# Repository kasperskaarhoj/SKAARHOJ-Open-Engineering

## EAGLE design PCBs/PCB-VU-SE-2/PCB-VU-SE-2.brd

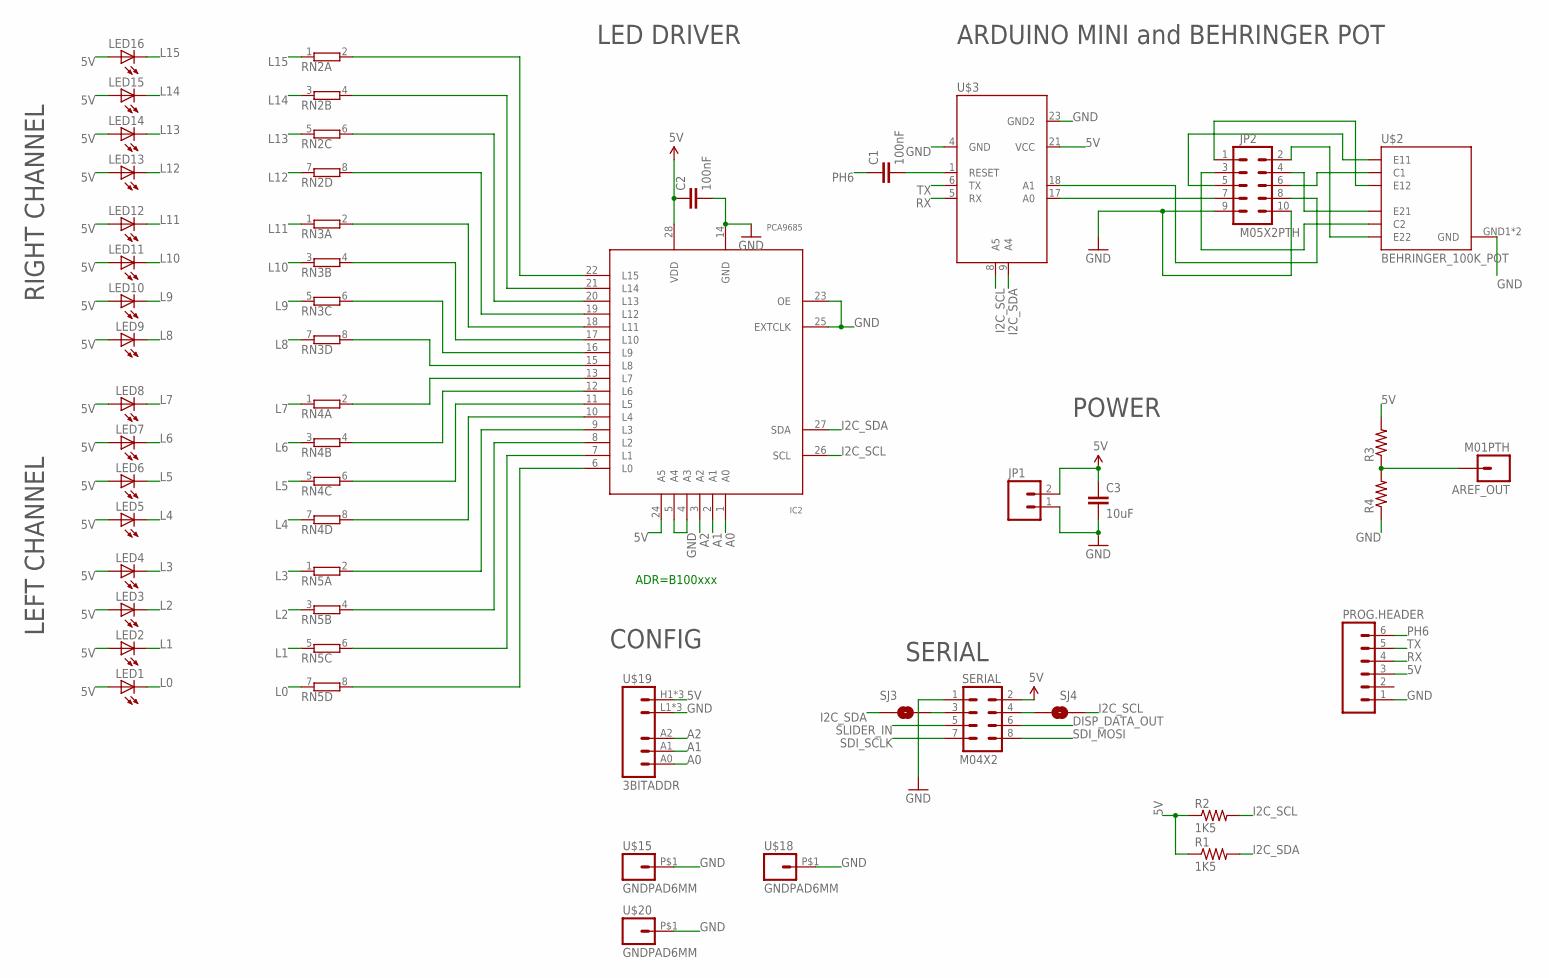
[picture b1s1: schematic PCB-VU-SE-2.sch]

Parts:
AREF_OUT: M01PTH; 1X01
C1, C2: 100nF; 0603-CAP
C3: 10uF; 0805
IC2: PCA9685; TSSOP28
JP1: M02PTH; 1X02
JP2: M05X2PTH; AVR_ICSP
LED1, LED2, LED3, LED4, LED5, LED6, LED7, LED8, LED9, LED10, LED11, LED12, LED13, LED14, LED15, LED16: LED3MM
PROG.HEADER: M06LOCK; 1X06_LOCK
R1, R2: 1K5; 0603-RES
R3, R4: RESISTOR0603-RES; 0603-RES
RN2, RN3, RN4, RN5: E4R; SIL8
SERIAL: M04X2; 2X4
SJ3, SJ4: SOLDERJUMPERNC; SJ_2S
U$2: BEHRINGER_100K_POT
U$3: ARDUINO_MINI_SE1
U$15, U$18, U$20: GNDPAD6MM; 3.2MMPAD6MM
U$19: 3BITADDR

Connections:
5V: C2.1, C3.1, IC2.24 (A5), IC2.28 (VDD), JP1.2, LED1.A, LED2.A, LED3.A, LED4.A, LED5.A, LED6.A, LED7.A, LED8.A, LED9.A, LED10.A, LED11.A, LED12.A, LED13.A, LED14.A, LED15.A, LED16.A, PROG.HEADER.3, R1.1, R2.1, R3.2, SERIAL.2, U$3.21 (VCC), U$19.H1 (VCC), U$19.H2 (VCC), U$19.H3 (VCC)
A0: IC2.1 (A0), U$19.A0
A1: IC2.2 (A1), U$19.A1
A2: IC2.3 (A2), U$19.A2
AREF: AREF_OUT.1, R3.1, R4.2
DISP_DATA_OUT: SERIAL.6
GND: C2.2, C3.2, IC2.4 (A3), IC2.5 (A4), IC2.14 (GND), IC2.23 (OE), IC2.25 (EXTCLK), JP1.1, JP2.9, JP2.10, PROG.HEADER.1, R4.1, SERIAL.1, U$2.GND1 (GND), U$2.GND2 (GND), U$3.4 (GND), U$3.23 (GND2), U$15.P$1, U$18.P$1, U$19.L1 (GND), U$19.L2 (GND), U$19.L3 (GND), U$20.P$1
I2C_SCL: IC2.26 (SCL), R2.2, SJ4.2, U$3.8 (A5)
I2C_SDA: IC2.27 (SDA), R1.2, SJ3.1, U$3.9 (A4)
L0: LED1.K (C), RN5.7 (1)
L1: LED2.K (C), RN5.5 (1)
L2: LED3.K (C), RN5.3 (1)
L3: LED4.K (C), RN5.1
L4: LED5.K (C), RN4.7 (1)
L5: LED6.K (C), RN4.5 (1)
L6: LED7.K (C), RN4.3 (1)
L7: LED8.K (C), RN4.1
L8: LED9.K (C), RN3.7 (1)
L9: LED10.K (C), RN3.5 (1)
L10: LED11.K (C), RN3.3 (1)
L11: LED12.K (C), RN3.1
L12: LED13.K (C), RN2.7 (1)
L13: LED14.K (C), RN2.5 (1)
L14: LED15.K (C), RN2.3 (1)
L15: LED16.K (C), RN2.1
unnamed: JP2.6, U$2.PAD1 (C1)
unnamed: JP2.4, U$2.PAD3 (E21)
unnamed: SERIAL.3, SJ3.2
unnamed: IC2.13 (L7), RN4.2
unnamed: IC2.12 (L6), RN4.4 (2)
unnamed: SERIAL.4, SJ4.1
unnamed: IC2.11 (L5), RN4.6 (2)
unnamed: JP2.3, U$2.PAD4 (C2)
unnamed: IC2.10 (L4), RN4.8 (2)
unnamed: IC2.9 (L3), RN5.2
unnamed: IC2.8 (L2), RN5.4 (2)
unnamed: IC2.7 (L1), RN5.6 (2)
unnamed: JP2.2, U$2.PAD5 (E22)
unnamed: JP2.5, U$2.PAD2 (E11)
unnamed: JP2.1, U$2.PAD6 (E12)
unnamed: JP2.8, U$3.18 (A1)
unnamed: JP2.7, U$3.17 (A0)
unnamed: IC2.6 (L0), RN5.8 (2)
unnamed: IC2.15 (L8), RN3.8 (2)
unnamed: IC2.16 (L9), RN3.6 (2)
unnamed: IC2.17 (L10), RN3.4 (2)
unnamed: IC2.18 (L11), RN3.2
unnamed: IC2.19 (L12), RN2.8 (2)
unnamed: IC2.20 (L13), RN2.6 (2)
unnamed: IC2.21 (L14), RN2.4 (2)
unnamed: IC2.22 (L15), RN2.2
unnamed: C1.2, U$3.1 (RESET)
PH6: C1.1, PROG.HEADER.6
RX: PROG.HEADER.4, U$3.5 (RX)
SDI_MOSI: SERIAL.8
SDI_SCLK: SERIAL.7
SLIDER_IN: SERIAL.5
TX: PROG.HEADER.5, U$3.6 (TX)

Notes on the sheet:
ADR=B100xxx
LED DRIVER
POWER
SERIAL
ARDUINO MINI and BEHRINGER POT
LEFT CHANNEL
RIGHT CHANNEL
CONFIG

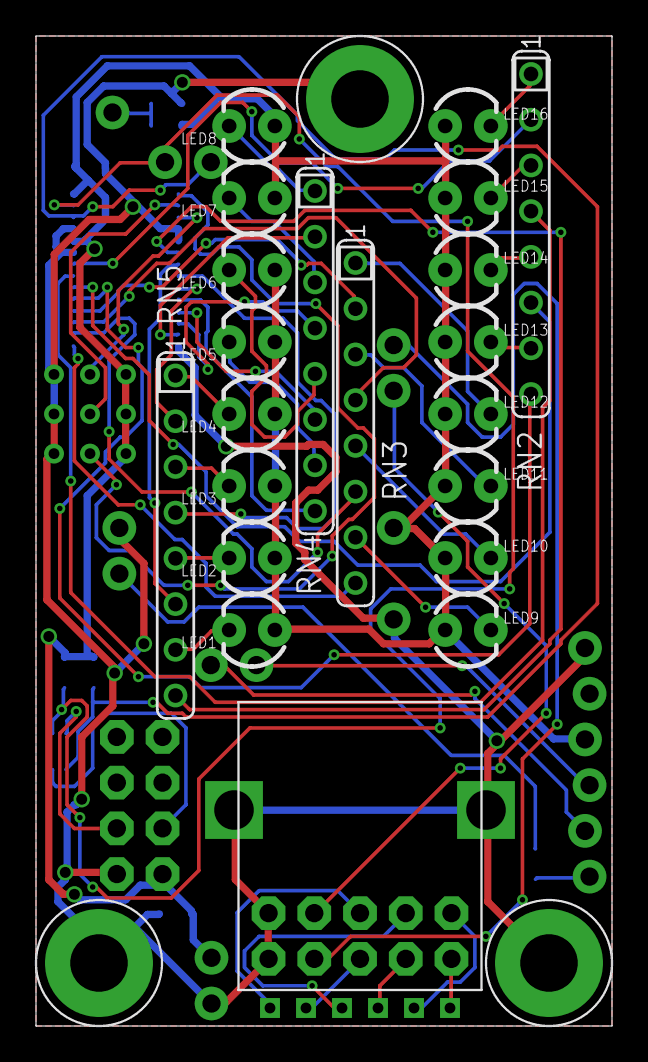
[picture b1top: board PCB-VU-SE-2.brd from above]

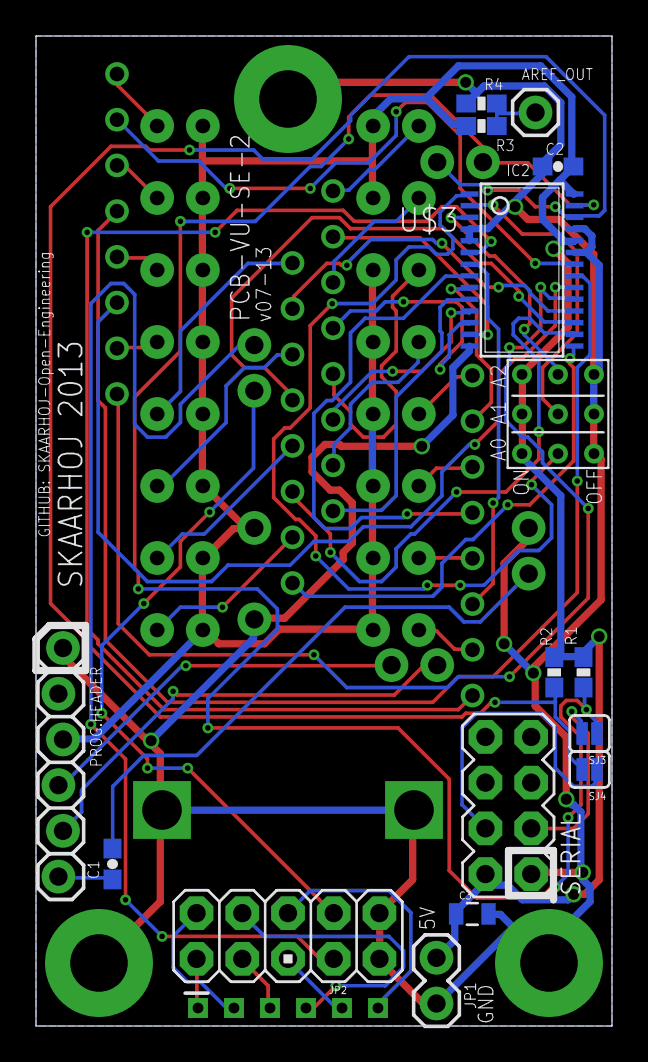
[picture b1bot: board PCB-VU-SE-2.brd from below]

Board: 2 copper layers, 32.0 x 55.0 mm, 41 parts (17 on the bottom side), 54 nets.

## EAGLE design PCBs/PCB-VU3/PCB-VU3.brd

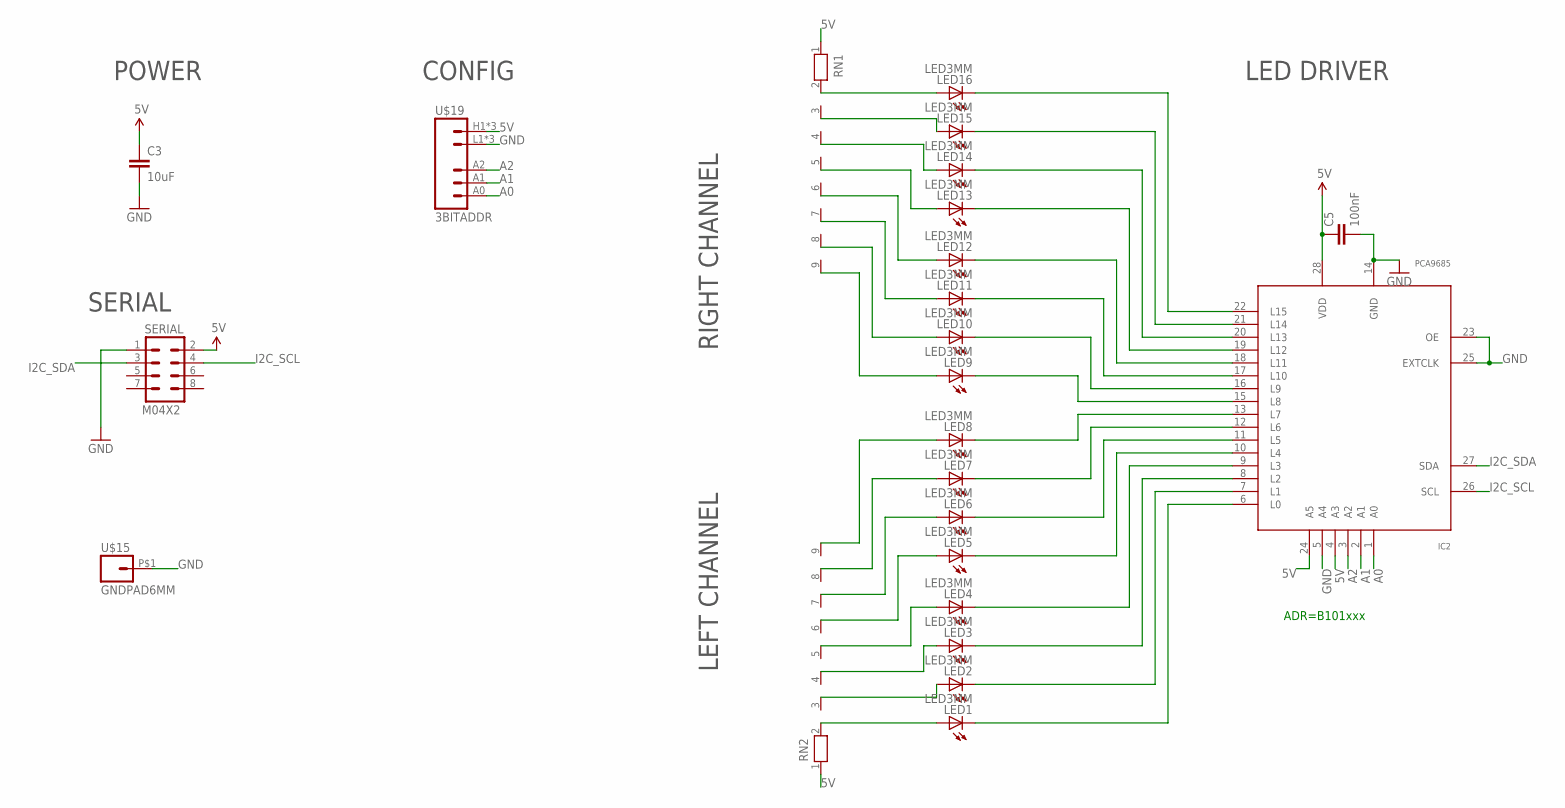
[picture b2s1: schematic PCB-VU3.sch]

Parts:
C3: 10uF; 0805
C5: 100nF; 0603-CAP
IC2: PCA9685; TSSOP28
LED1, LED2, LED3, LED4, LED5, LED6, LED7, LED8, LED9, LED10, LED11, LED12, LED13, LED14, LED15, LED16: LED3MM
RN1, RN2: RN08; RN-9
SERIAL: M04X2; 2X4
U$15: GNDPAD6MM; 3.2MMPAD6MM
U$19: 3BITADDR

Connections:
5V: C3.1, C5.1, IC2.4 (A3), IC2.24 (A5), IC2.28 (VDD), RN1.1, RN2.1, SERIAL.2, U$19.H1 (VCC), U$19.H2 (VCC), U$19.H3 (VCC)
A0: IC2.1 (A0), U$19.A0
A1: IC2.2 (A1), U$19.A1
A2: IC2.3 (A2), U$19.A2
GND: C3.2, C5.2, IC2.5 (A4), IC2.14 (GND), IC2.23 (OE), IC2.25 (EXTCLK), SERIAL.1, U$15.P$1, U$19.L1 (GND), U$19.L2 (GND), U$19.L3 (GND)
I2C_SCL: IC2.26 (SCL), SERIAL.4
I2C_SDA: IC2.27 (SDA), SERIAL.3
unnamed: IC2.13 (L7), LED8.K (C)
unnamed: LED16.A, RN1.2
unnamed: LED15.A, RN1.3
unnamed: LED14.A, RN1.4
unnamed: LED13.A, RN1.5
unnamed: LED12.A, RN1.6
unnamed: LED11.A, RN1.7
unnamed: LED10.A, RN1.8
unnamed: LED9.A, RN1.9
unnamed: LED1.A, RN2.2
unnamed: LED2.A, RN2.3
unnamed: LED3.A, RN2.4
unnamed: LED4.A, RN2.5
unnamed: LED5.A, RN2.6
unnamed: LED6.A, RN2.7
unnamed: IC2.12 (L6), LED7.K (C)
unnamed: IC2.11 (L5), LED6.K (C)
unnamed: IC2.10 (L4), LED5.K (C)
unnamed: IC2.9 (L3), LED4.K (C)
unnamed: IC2.8 (L2), LED3.K (C)
unnamed: IC2.7 (L1), LED2.K (C)
unnamed: IC2.6 (L0), LED1.K (C)
unnamed: IC2.15 (L8), LED9.K (C)
unnamed: IC2.16 (L9), LED10.K (C)
unnamed: IC2.17 (L10), LED11.K (C)
unnamed: IC2.18 (L11), LED12.K (C)
unnamed: IC2.19 (L12), LED13.K (C)
unnamed: IC2.20 (L13), LED14.K (C)
unnamed: IC2.21 (L14), LED15.K (C)
unnamed: IC2.22 (L15), LED16.K (C)
unnamed: LED7.A, RN2.8
unnamed: LED8.A, RN2.9

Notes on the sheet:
SERIAL
POWER
ADR=B101xxx
LED DRIVER
LEFT CHANNEL
RIGHT CHANNEL
CONFIG

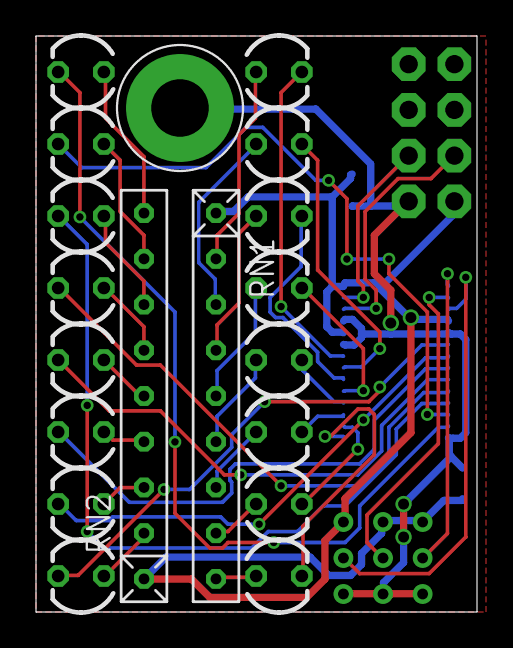
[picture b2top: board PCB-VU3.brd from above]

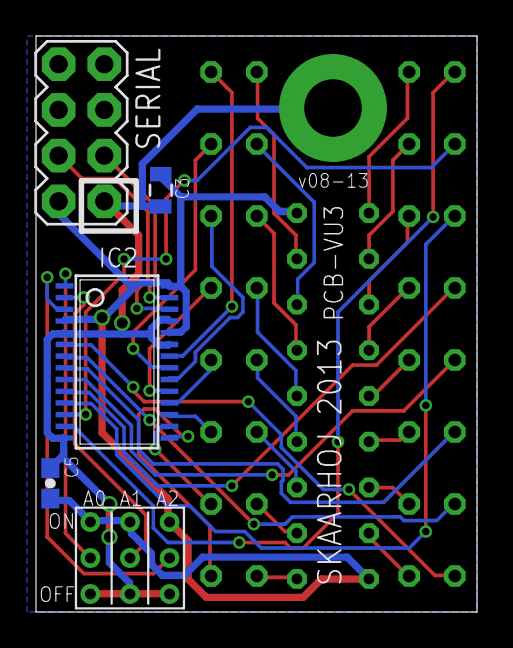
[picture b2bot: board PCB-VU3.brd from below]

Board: 2 copper layers, 24.5 x 32.0 mm, 24 parts (5 on the bottom side), 39 nets.

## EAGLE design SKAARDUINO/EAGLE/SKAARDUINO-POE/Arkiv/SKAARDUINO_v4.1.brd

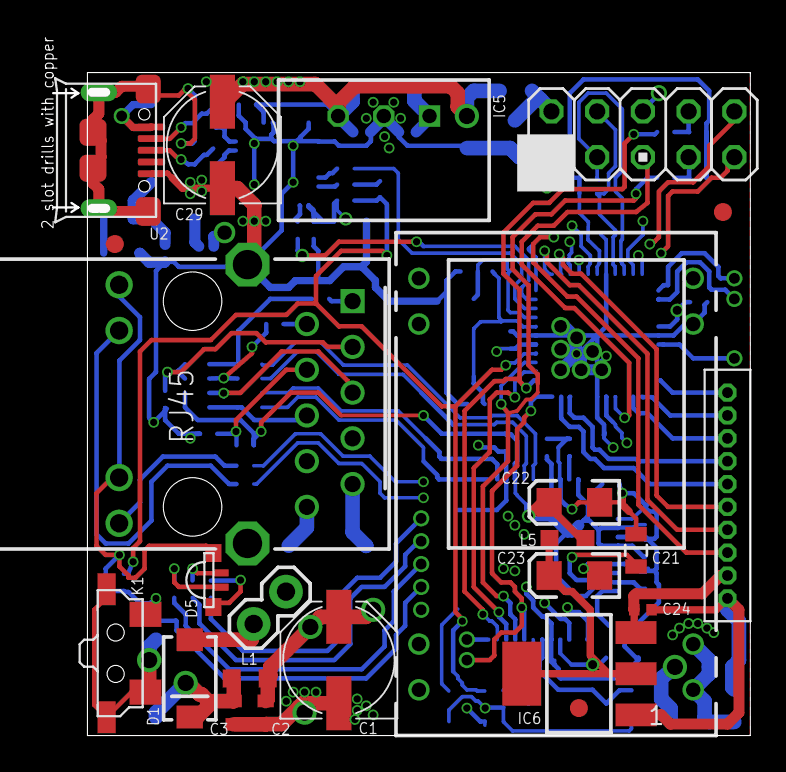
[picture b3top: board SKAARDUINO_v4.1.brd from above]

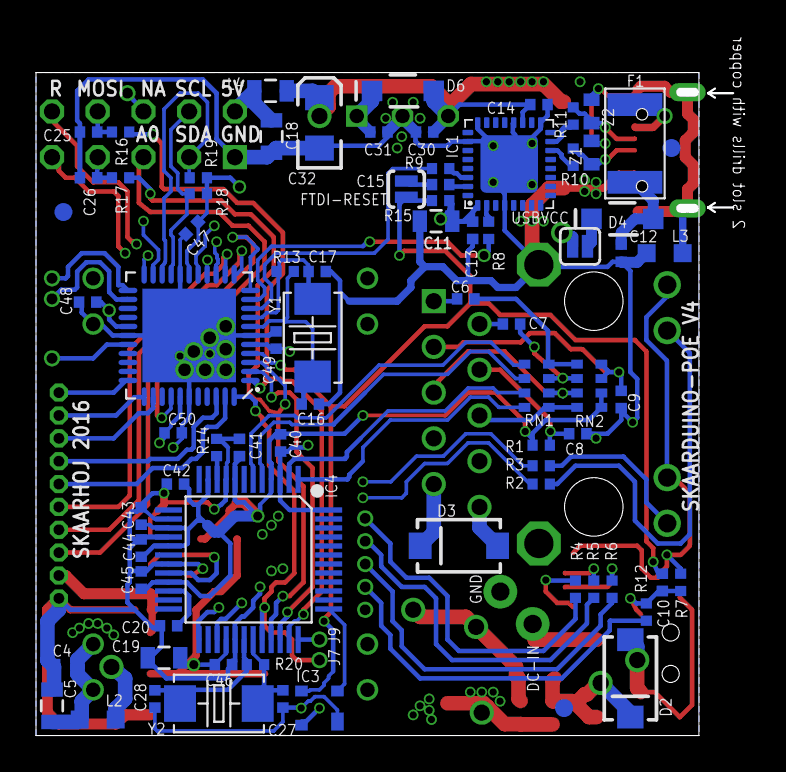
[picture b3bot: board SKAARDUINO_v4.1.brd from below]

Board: 4 copper layers, 38.7 x 36.8 mm, 114 parts (79 on the bottom side), 81 nets.

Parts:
C1: 100uF/25V; PANASONIC_D
C2, C3, C4: 100nF/25V; C0402
C5: 10uF/25V; 0805
C6, C7: 6.8nF; 0402C
C8: 22nF; 0402C
C9, C20: 10nF; 0402C
C10, C12: 1uF; 0402C
C11: 22uF; 0805
C13, C14, C15, C24, C30, C40, C41, C42, C43, C44, C45, C46, C47, C48, C49, C50: 100nF; 0402C
C16, C17, C25, C26: 22pF; 0402C
C18: 22uF/6.3V; 0805
C19: 10uF/16V; 0805
C21: 4.7uF; 0805
C22, C23, C32: 10uF 6.3V A TANT; EIA3216
C27, C28: 18pF; 0402C
C29: 330uF/6.3V; PANASONIC_D
C31: 100nF/25V; 0402C
D1: MBRA210LT3G; SMA-DIODE
D2, D3: SMAJ58CA; SMA-DIODE
D4, D6: MBR0520; SOD-123
D5: KPFA-3010RGBC-11; LED-TRICOLOR-SMD
F1: SMD-PPTC-500MA-15V(1812); F1812
FID1, FID2, FID3, FID4, FID5, FID8: FIDUCIAL1X2.5; FIDUCIAL-1X2.5
FTDI-RESET: SOLDERJUMPERNO; SJ_2S-NO
IC1: FT232RQ; QFN32
IC2: ATMEGA1284P; QFN-44M1
IC3: APX811-44UG-7; SOT143-R
IC4: WizNet W5500; LQFP-48
IC5: RECOM 785.0-1.0; RECOM_785.0-1.0
IC6: LD1117S33CTR; SOT-223
J1, J3, J4, J6, J7, J13, J14: SS; M1X1
J2: DC IN JACK; 1X02
J5: M04X2M2X4SMALLER; M2X4SMALLER
J8: M10_1.27; M10X1
J9: W_INT; M1X1
J10: D11; M1X1
J11: D12; M1X1
J12: AREF; M1X1
JP1: M01X2; M2X1SMALLER
K1: RESET/CFG; SW4-SMD-7.0X3.5X3.5MM-90D
L1, L2, L3: Bead ILHB0805ER121V; L2012C
L4: Bead ILHB0805ER121V; 0805
L5: 1uH 250mA 0805; L2012C
R1: 10R/1%; 0402
R2, R3: 470R; 0402
R4: 390R; 0402
R5: 540R; 0402
R6: 2K7; 0402
R7, R15: 10K; 0402
R8, R9: 1K; 0402
R10, R11: 22R; 0402
R12: 100K; 0402
R13, R20: 1M; 0402
R14: 12K4 / 1%; 0402
R16, R17: 100R; 0402
R18, R19: 1K5; 0402
RN1: 33R; CAY16
RN2: 49R9 1%; CAY16
U1: HY931147C-RJ45; HY931147C
U2: MICRO USB; MICRO-USB5+4P-SMD-0.65-B
U$7: AG9800PTH
USBVCC: SOLDERJUMPERNC; SJ_2S
Y1: 20MhZ; X2-SMD-5.0X3.2X1.3MM
Y2: 25MhZ; X2-SMD-5.0X3.2X1.3MM
Z1, Z2: PGB1010603; C0402

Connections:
3V3A: C22.A, C40.1, C41.1, C42.1, C43.1, C44.1, C45.1, IC4.4, IC4.8, IC4.11, IC4.15, IC4.17, IC4.21, L5.2, R1.2, RN2.5, RN2.6
3V3D: C19.1, C23.A, C46.1, IC4.28, IC6.2, IC6.TER, L5.1
5V: C11.1, C13.2, C14.2, C24.1, C29.+, C30.1, C32.A, C47.1, C48.1, C49.1, C50.1, D5.A, D6.2, IC1.1, IC1.19, IC2.5, IC2.17, IC2.27, IC2.38, IC3.4, IC5.P$3, IC6.3, J8.2, L4.2, R7.2, R15.2, R18.2, R19.2, U1.P$11, U1.P$13, USBVCC.2
A0: IC2.37, J5.5
A2: IC2.35, J8.8
A3: IC2.34, J8.9
A4: IC2.33, J8.10
ACTLED: IC4.27, R3.1
CFG: IC2.21, J4.1, R12.1
CFGSW: C10.2, K1.1, R7.1, R12.2
D0_RX: IC2.9, R9.2
D1_TX: IC2.10, R8.2
D2: IC2.11, J8.3
D3: IC2.12, J8.4
D4: IC2.13, J8.5
D5: IC2.14, J13.1, R4.1
D6: IC2.15, J1.1, R5.1
D7: IC2.16, J3.1, R6.1
D8: IC2.42, J8.7
D9: IC2.43, J8.6
D10: IC2.22, J6.1
D10_SS: IC2.44, IC4.32, J7.1
D11: IC2.23, J10.1
D11_MOSI: IC2.1, IC4.35, R16.2
D12: IC2.24, J11.1
D12_MISO: IC2.2, IC4.34, JP1.1
D13_SCK: IC2.3, IC4.33, R17.2
GND: C1.-, C2.2, C3.2, C4.2, C5.2, C8.1, C9.1, C11.2, C12.1, C13.1, C14.1, C16.1, C17.1, C18.1, C19.2, C20.2, C21.2, C22.C, C23.C, C24.2, C25.1, C26.1, C27.1, C28.1, C29.-, C30.2, C31.2, C32.C, C40.2, C41.2, C42.2, C43.2, C44.2, C45.2, C46.2, C47.2, C48.2, C49.2, C50.2, D2.A, IC1.4, IC1.17, IC1.20, IC1.24, IC1.26, IC2.6, IC2.18, IC2.28, IC2.39, IC2.TGND, IC3.1, IC4.3, IC4.9, IC4.14, IC4.16, IC4.19, IC4.29, IC4.48, IC5.P$2, IC6.1, J2.2, J5.1, J8.1, K1.2, K1.S1, K1.S2, L3.2, R14.1, U1.GND1, U1.GND2, U2.5, U$7.P3
I2C_SCL: IC2.19, J5.4, R18.1
I2C_SDA: IC2.20, J5.3, R19.1
LINKLED: IC4.25, R2.1
MOSI: C25.2, J5.8, R16.1
unnamed: C8.2, R1.1, U1.P$4
unnamed: C15.2, FTDI-RESET.1
unnamed: D5.B, R6.2
unnamed: C3.1, D1.C, D2.C, L1.1
unnamed: D5.G, R5.2
unnamed: C12.2, D4.2, F1.2
unnamed: F1.1, U2.1
unnamed: C16.2, IC2.7, R13.2, Y1.2
unnamed: C7.2, U1.P$2
unnamed: J5.6, J14.1
unnamed: C6.2, U1.P$1
unnamed: C17.2, IC2.8, R13.1, Y1.1
unnamed: D1.A, J2.1
unnamed: D5.R, R4.2
unnamed: R10.2, U2.3, Z1.1
unnamed: R11.2, U2.2, Z2.1
unnamed: C15.1, IC1.31
unnamed: C18.2, J5.2, L4.1
unnamed: C21.1, IC4.20
unnamed: L3.1, U2.S1, U2.S2, U2.S3, U2.S4, U2.S5, U2.S6, Z1.2, Z2.2
unnamed: C20.1, IC4.22
unnamed: IC4.10, R14.2
unnamed: IC4.36, J9.1
unnamed: IC2.29, J12.1
unnamed: R3.2, U1.P$14
unnamed: C9.2, RN2.7, RN2.8, U1.P$3
unnamed: R2.2, U1.P$12
POE_DC_RETURN: C4.1, C5.1, L2.1, U$7.P1, U$7.P2
POE_VIN+: D3.C, U1.P$9, U$7.P5, U$7.P6
POE_VIN-: D3.A, U1.P$10, U$7.P7, U$7.P8
RD+: IC1.14, R10.1
RD-: IC1.15, R11.1
RESET: C10.1, FTDI-RESET.2, IC2.4, IC3.3, JP1.2, R15.1
RXIN: IC4.5, RN1.6
RXIN_E: C7.1, RN1.3, RN2.2
RXIP: IC4.6, RN1.5
RXIP_E: C6.1, RN1.4, RN2.1
SCLK: C26.2, J5.7, R17.1
TXON: IC4.1, RN1.8
TXON_E: RN1.1, RN2.4, U1.P$6
TXOP: IC4.2, RN1.7
TXOP_E: RN1.2, RN2.3, U1.P$5
USBRXD: IC1.30, R9.1
USBTXD: IC1.2, R8.1
USBVCC: D4.1, USBVCC.1
VIN: C1.+, C2.1, C31.1, D6.1, IC5.P$1, L1.2, L2.2
WIZRST: IC3.2, IC4.37
XTLN: C28.2, IC4.30, R20.2, Y2.2
XTLP: C27.2, IC4.31, R20.1, Y2.1

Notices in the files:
parts and their libraries:
SparkFun: Licensing: CC v3.0 Share-Alike You are welcome to use this library for commercial purposes.
